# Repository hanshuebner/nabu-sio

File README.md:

# nabu-sio

Dual port serial card for the NABU PC, based on Z80 SIO & Z80 CTC.

Work in progress, don't use it yet.

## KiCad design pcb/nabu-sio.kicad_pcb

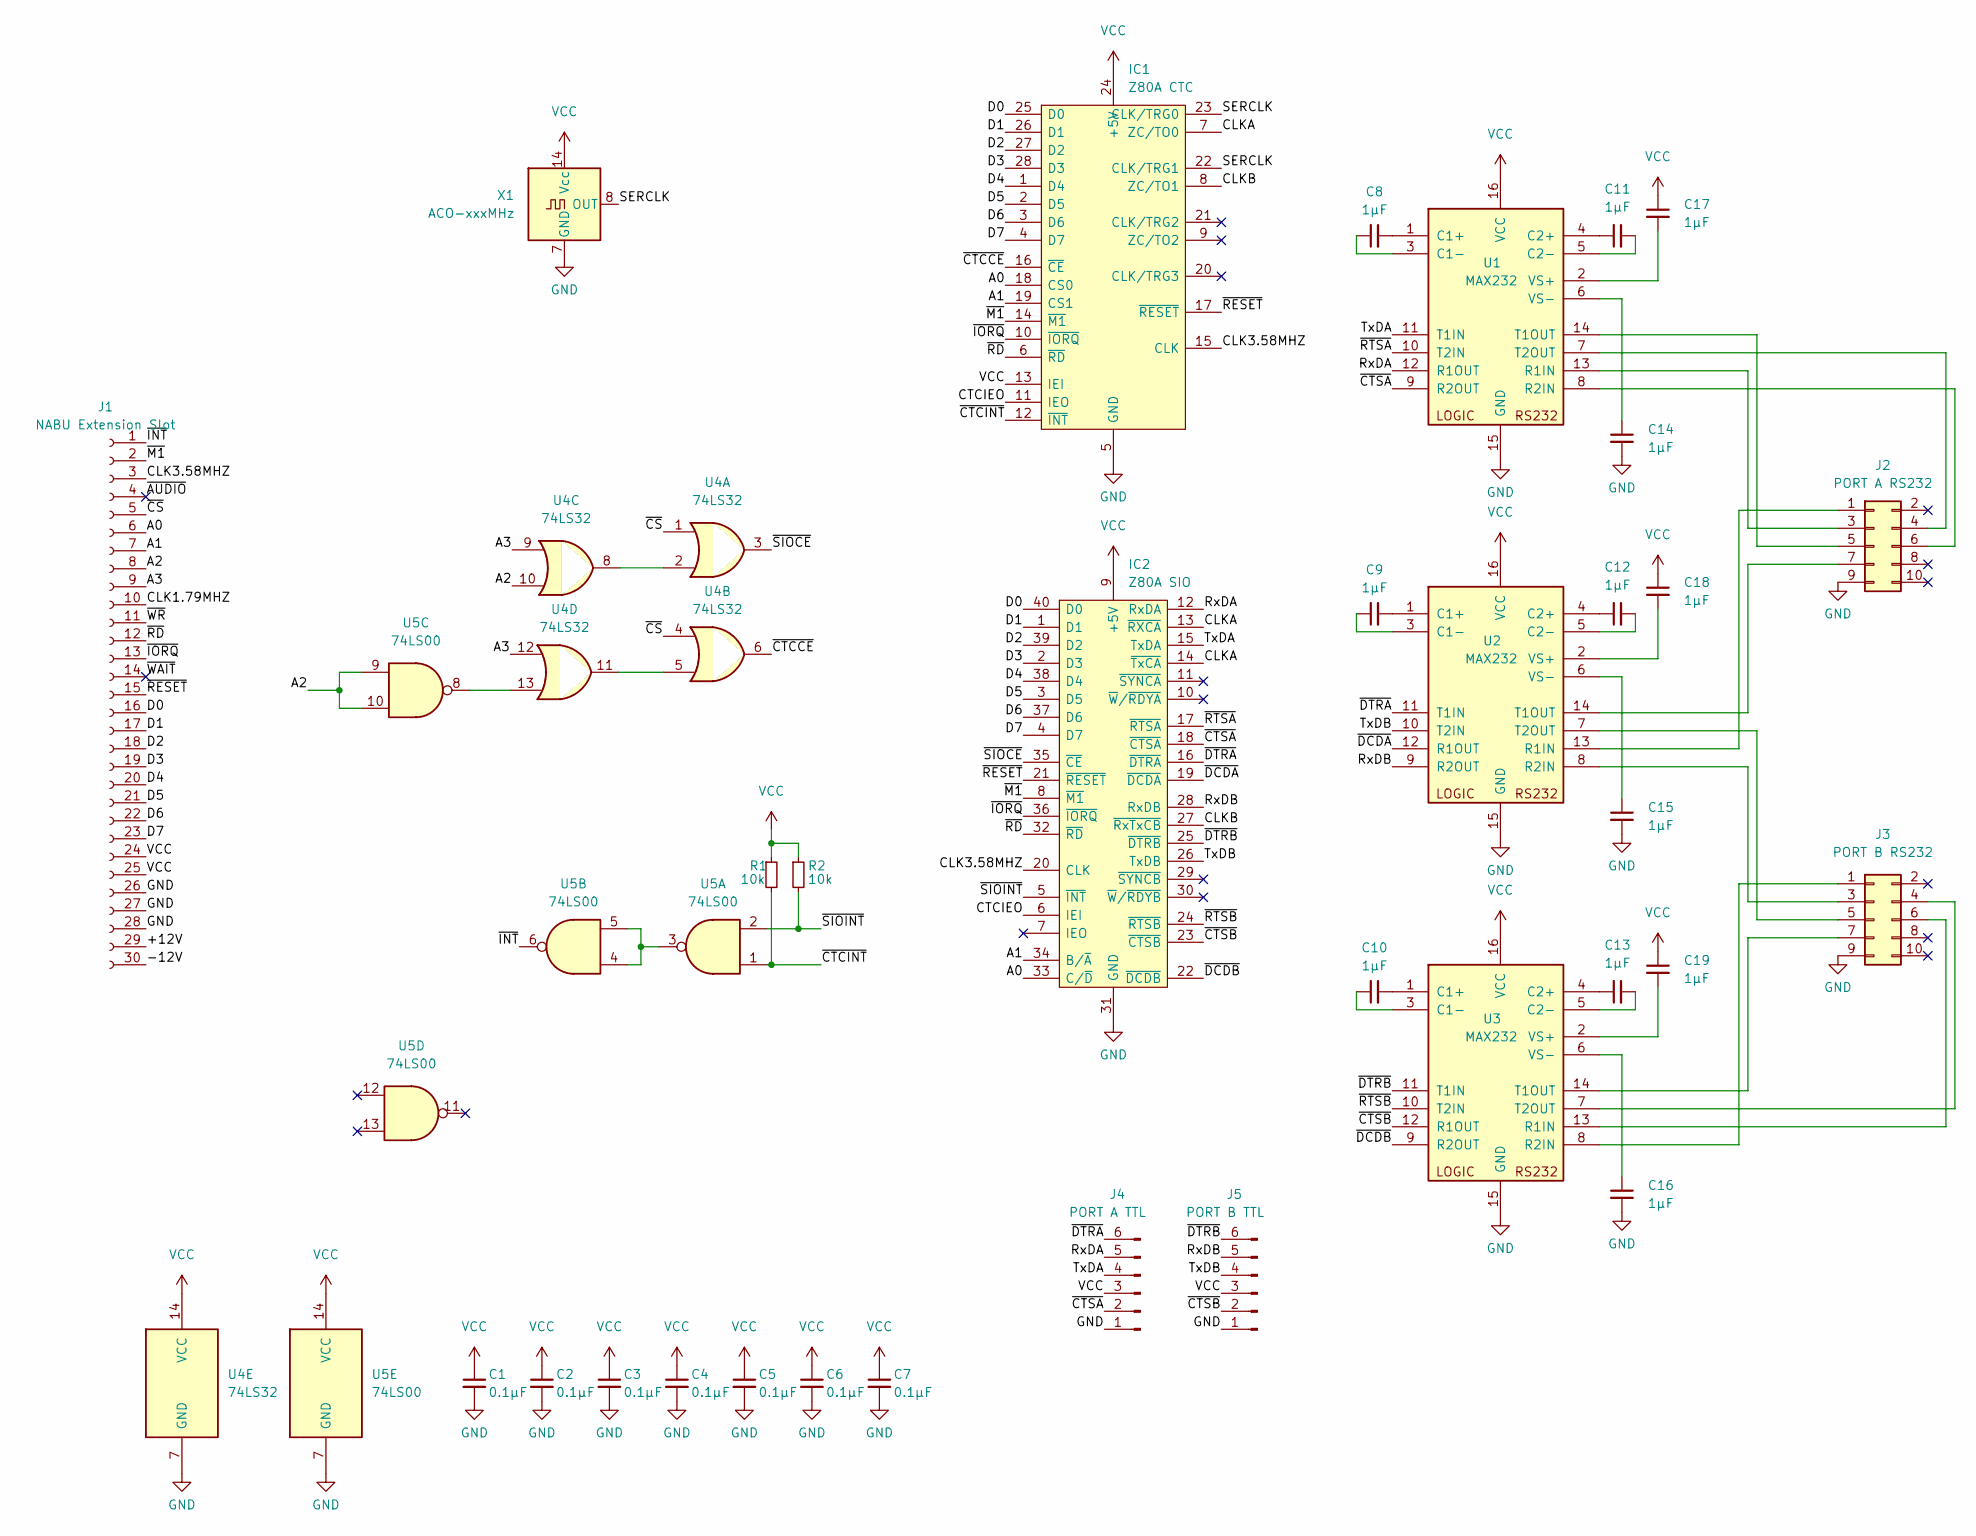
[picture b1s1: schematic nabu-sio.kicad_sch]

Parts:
C1, C2, C3, C4, C5, C6, C7: 0.1µF; C_0603_1608Metric_Pad1.08x0.95mm_HandSolder
C8, C9, C10, C11, C12, C13, C14, C15, C16, C17, C18, C19: 1µF; C_0603_1608Metric_Pad1.08x0.95mm_HandSolder
IC1: Z80A CTC; DIP-28_W15.24mm_LongPads; Manufacturer_Part_Number Z84C3010PEG; Mouser Part Number 692-Z84C3010PEG
IC2: Z80A SIO; DIP-40_W15.24mm_LongPads; Manufacturer_Part_Number Z84C4206PEG; Mouser Part Number 692-Z84C4206PEG
J1: NABU Extension Slot; PinSocket_1x30_P2.54mm_Vertical
J2: PORT A RS232; PinHeader_2x05_P2.54mm_Horizontal
J3: PORT B RS232; PinHeader_2x05_P2.54mm_Horizontal
J4: PORT A TTL; PinHeader_1x06_P2.54mm_Horizontal
J5: PORT B TTL; PinHeader_1x06_P2.54mm_Horizontal
R1, R2: 10k; R_0603_1608Metric_Pad0.98x0.95mm_HandSolder
U1, U2, U3: MAX232; SOP-16_4.55x10.3mm_P1.27mm
U4: 74LS32; SOP-14_4.55x10.3mm_P1.27mm
U5: 74LS00; SOP-14_4.55x10.3mm_P1.27mm
X1: ACO-xxxMHz; Oscillator_DIP-14

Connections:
/+12V: J1.29 (+12V)
/-12V: J1.30 (-12V)
/A0: IC1.18 (CS0), IC2.33 (C/~D), J1.6 (A0)
/A1: IC1.19 (CS1), IC2.34 (B/~A), J1.7 (A1)
/A2: J1.8 (A2), U4.10, U5.9, U5.10
/A3: J1.9 (A3), U4.9, U4.12
/CLK1.79MHZ: J1.10 (1.79)
/CLK3.58MHZ: IC1.15 (CLK), IC2.20 (CLK), J1.3 (3.58)
/CLKA: IC1.7 (ZC/TO0), IC2.13 (~RXCA), IC2.14 (~TxCA)
/CLKB: IC1.8 (ZC/TO1), IC2.27 (~RxTxCB)
/CTCIEO: IC1.11 (IEO), IC2.6 (IEI)
/D0: IC1.25 (D0), IC2.40 (D0), J1.16 (D0)
/D1: IC1.26 (D1), IC2.1 (D1), J1.17 (D1)
/D2: IC1.27 (D2), IC2.39 (D2), J1.18 (D2)
/D3: IC1.28 (D3), IC2.2 (D3), J1.19 (D3)
/D4: IC1.1 (D4), IC2.38 (D4), J1.20 (D4)
/D5: IC1.2 (D5), IC2.3 (D5), J1.21 (D5)
/D6: IC1.3 (D6), IC2.37 (D6), J1.22 (D6)
/D7: IC1.4 (D7), IC2.4 (D7), J1.23 (D7)
/RxDA: IC2.12 (RxDA), J4.5, U1.12 (R1OUT)
/RxDB: IC2.28 (RxDB), J5.5, U2.9 (R2OUT)
/SERCLK: IC1.22 (CLK/TRG1), IC1.23 (CLK/TRG0), X1.8 (OUT)
/TxDA: IC2.15 (TxDA), J4.4, U1.11 (T1IN)
/TxDB: IC2.26 (TxDB), J5.4, U2.10 (T2IN)
/~AUDIO: J1.4 (AUDIO)
/~CS: J1.5 (~CS), U4.1, U4.4
/~CTCCE: IC1.16 (~CE), U4.6
/~CTCINT: IC1.12 (~INT), R1.2, U5.1
/~CTSA: IC2.18 (~CTSA), J4.2, U1.9 (R2OUT)
/~CTSB: IC2.23 (~CTSB), J5.2, U3.12 (R1OUT)
/~DCDA: IC2.19 (~DCDA), U2.12 (R1OUT)
/~DCDB: IC2.22 (~DCDB), U3.9 (R2OUT)
/~DTRA: IC2.16 (~DTRA), J4.6, U2.11 (T1IN)
/~DTRB: IC2.25 (~DTRB), J5.6, U3.11 (T1IN)
/~INT: J1.1 (~INT), U5.6
/~IORQ: IC1.10 (~IORQ), IC2.36 (~IORQ), J1.13 (~IORQ)
/~M1: IC1.14 (~M1), IC2.8 (~M1), J1.2 (~M1)
/~RD: IC1.6 (~RD), IC2.32 (~RD), J1.12 (~RD)
/~RESET: IC1.17 (~RESET), IC2.21 (~RESET), J1.15 (~RESET)
/~RTSA: IC2.17 (~RTSA), U1.10 (T2IN)
/~RTSB: IC2.24 (~RTSB), U3.10 (T2IN)
/~SIOCE: IC2.35 (~CE), U4.3
/~SIOINT: IC2.5 (~INT), R2.2, U5.2
/~WAIT: J1.14 (~WAIT)
/~WR: J1.11 (~WR)
GND: C1.2, C2.2, C3.2, C4.2, C5.2, C6.2, C7.2, C14.2, C15.2, C16.2, IC1.5 (GND), IC2.31 (GND), J1.26 (GND), J1.27 (GND), J1.28 (GND), J2.9, J3.9, J4.1, J5.1, U1.15 (GND), U2.15 (GND), U3.15 (GND), U4.7 (GND), U5.7 (GND), X1.7 (GND)
unnamed: C8.1, U1.3 (C1-)
unnamed: C8.2, U1.1 (C1+)
unnamed: C9.1, U2.3 (C1-)
unnamed: C9.2, U2.1 (C1+)
unnamed: C10.1, U3.3 (C1-)
unnamed: C10.2, U3.1 (C1+)
unnamed: C11.1, U1.4 (C2+)
unnamed: C11.2, U1.5 (C2-)
unnamed: C12.1, U2.4 (C2+)
unnamed: C12.2, U2.5 (C2-)
unnamed: C13.1, U3.4 (C2+)
unnamed: C13.2, U3.5 (C2-)
unnamed: C14.1, U1.6 (VS-)
unnamed: C15.1, U2.6 (VS-)
unnamed: C16.1, U3.6 (VS-)
unnamed: C17.2, U1.2 (VS+)
unnamed: C18.2, U2.2 (VS+)
unnamed: C19.2, U3.2 (VS+)
unnamed: J2.1, U2.13 (R1IN)
unnamed: J2.3, U1.13 (R1IN)
unnamed: J2.4, U1.7 (T2OUT)
unnamed: J2.5, U1.14 (T1OUT)
unnamed: J2.6, U1.8 (R2IN)
unnamed: J2.7, U2.14 (T1OUT)
unnamed: J3.1, U3.8 (R2IN)
unnamed: J3.3, U2.8 (R2IN)
unnamed: J3.4, U3.7 (T2OUT)
unnamed: J3.5, U2.7 (T2OUT)
unnamed: J3.6, U3.13 (R1IN)
unnamed: J3.7, U3.14 (T1OUT)
unnamed: U4.2, U4.8
unnamed: U4.5, U4.11
unnamed: U4.13, U5.8
unnamed: U5.3, U5.4, U5.5
VCC: C1.1, C2.1, C3.1, C4.1, C5.1, C6.1, C7.1, C17.1, C18.1, C19.1, IC1.13 (IEI), IC1.24 (+5V), IC2.9 (+5V), J1.24 (+5V), J1.25 (+5V), J4.3, J5.3, R1.1, R2.1, U1.16 (VCC), U2.16 (VCC), U3.16 (VCC), U4.14 (VCC), U5.14 (VCC), X1.14 (Vcc)

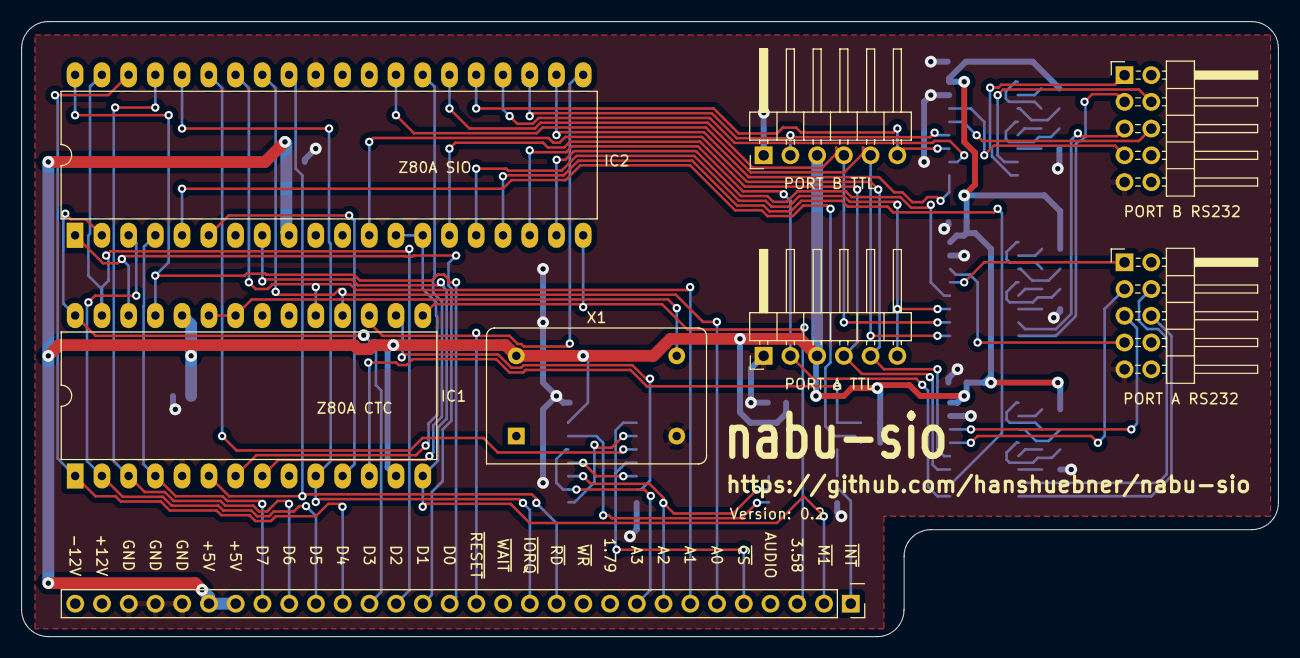
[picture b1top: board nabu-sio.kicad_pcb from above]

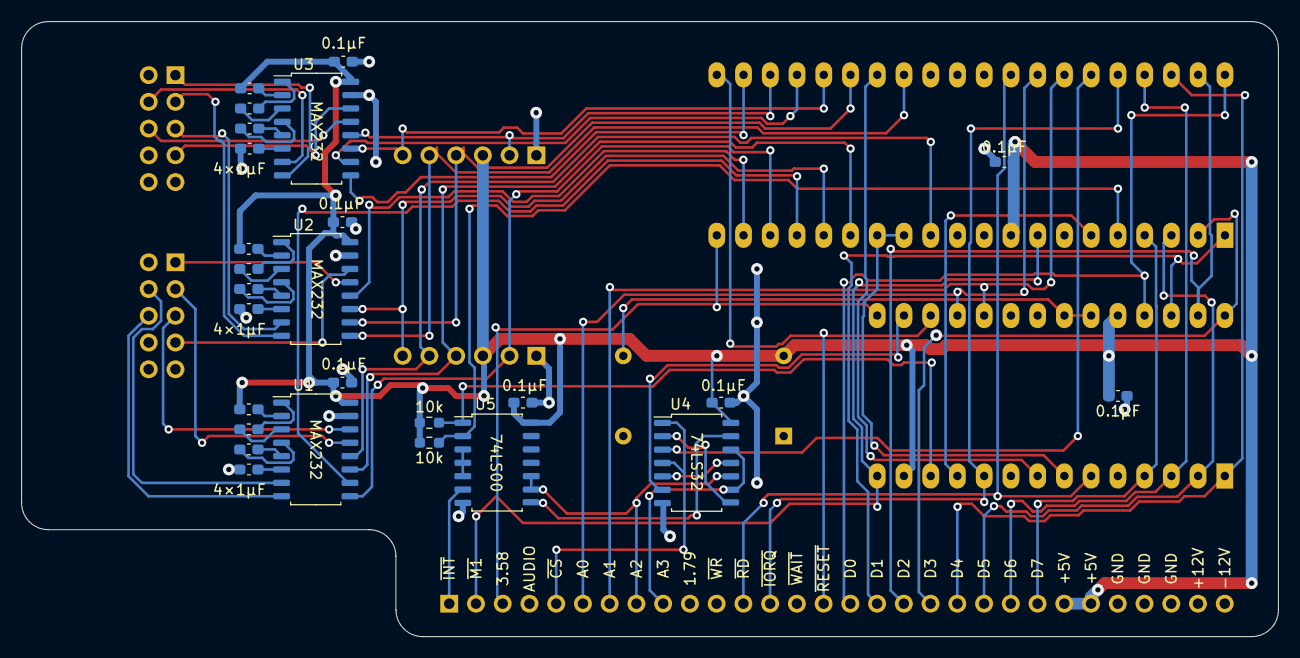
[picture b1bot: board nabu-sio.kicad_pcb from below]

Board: 2 copper layers, 119.4 x 58.4 mm, 34 parts (26 on the bottom side), 75 nets.

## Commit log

2023-02-02 Initial version
2023-02-02 Version 0.1 sent to production
2023-02-02 Fix some labels
2023-02-02 add images
2023-02-02 Various fixes
2023-02-02 Update gerbers
2023-02-02 Update images
